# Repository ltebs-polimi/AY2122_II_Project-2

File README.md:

# ELECTRONIC TECHNOLOGIES AND BIOSENSORS LABORATORY, a.a. 2021/22

# Project 2 - Colombo L., D'Andrea M.

## Objective of the project

The objective of the project is to design and develop a system able to perform glucose monitoring using PSoC 5 as a potentiostat. Internal subdivision of the repository is as following:

- Case: contains the .stl files for the case design and printing
- Documents: contains all the bibliography related to the project and the datasheets of the hardware components
- Group2.cydsn: backup folder containing only the code related to glucose measurement, peripherals not included. **It is not to be intended as the folder of the whole project**
- PCB: contains schematic and board files for the PCB of the device
- Presentations: contains images of the project and final presentation
- Project_design: folder of the actual project
- PYTHON GUI: folder containing python scripts for the GUI
- Regression: folder containing the regression script used to find a calibration line and related images

**To open and run the project, open the Project_ETBL.cywrk file**

## Features implemented

Besides being capable of performing glucose measurements, the device hardware includes:

- RTC (DS3231): for real time tracking
- Bluetooth BR/EDR module (HC-05): for wireless communication
- External battery
- OLED screen (SSD1306 by Adafruit): to visualize data when GUI is not active
- External EEPROM (24LC512 by MicroChip): to store measurements

The assembled device and PCB are in the following images:
<br>

<br><br>

<br>

<br><br>

## PSoC code
The PSoC code is composed by:

- A global switch case handling the passage between the different OLED screens, up to the "Press the button to START the measurement" screen

- When the hardware button is pressed, the code automatically fetches potential values from the EEPROM and starts and amperometry scan. Basically "adcDacInterrupt" scans
a look-up table and sets the values to the DAC. At the same time the "adcAmpInterrupt" converts the values read by the ADC into current. In the end a glucose 
concentration value is retrieved by means of a proper calibration curve and the result is shown on the OLED screen.

- In case the GUI is started, the code allows to have a connection to the GUI and all the possible commands are managed. Among the different possibilities:
    - cyclic voltammetry (CV): another look up table is scanned by "dacInterrupt" and the "adcInterrupt" convertes the ADC readings into current. These values are sent to the GUI via bluetooth
    - chronoamperometry (CA): same as described before but in this case the current values are sent via bluetooth to the GUI
    - measurements history: measurements which were saved into the EEPROM (date, time and glucose value) at the end of a CA, are sent to the GUI via bluetooth

**see "GUI code" for further details**

## GUI code
The GUI is based on 3 different screens:

- first_screen.py: it allows to select between a user and a clinician

- user_screen.py:
    - Automatic COM port detection by sending a proper command to the PSoC and waiting for the expected answer
    - By pressing the "START MEASUREMENT" button, only a chronoamperometry will be started by sending a proper command to the psoc. The two ISRs needed for the chronoamperometry will be started. Finally the result of the measurement is displayed

- clinician_screen.py: 
    - Automatic COM port detection by sending a proper command to the PSoC and waiting for the expected answer
    - First tab (cyclic voltammetry): it is possible to setup all the required parameters for a cyclic voltammetry. Then it allows to visualize a real-time
    graph by pressing "DRAW"
    - Second tab (chronoamperometry): The clinician can decide to fetch a value of potential from the EEPROM or to start a CA based on the peak of potential identified 
    by the previous cyclic voltammetry. In both cases the real-time graph is shown
    - Third screen (Data visualization): it displays the result of the chronoamperometry scan, in terms of glucose concentration
    - Fourth tab (History): it allows to check the three latest measurements taken by the device. There is also the indication about the date and the time at which the 
    measurements have been taken

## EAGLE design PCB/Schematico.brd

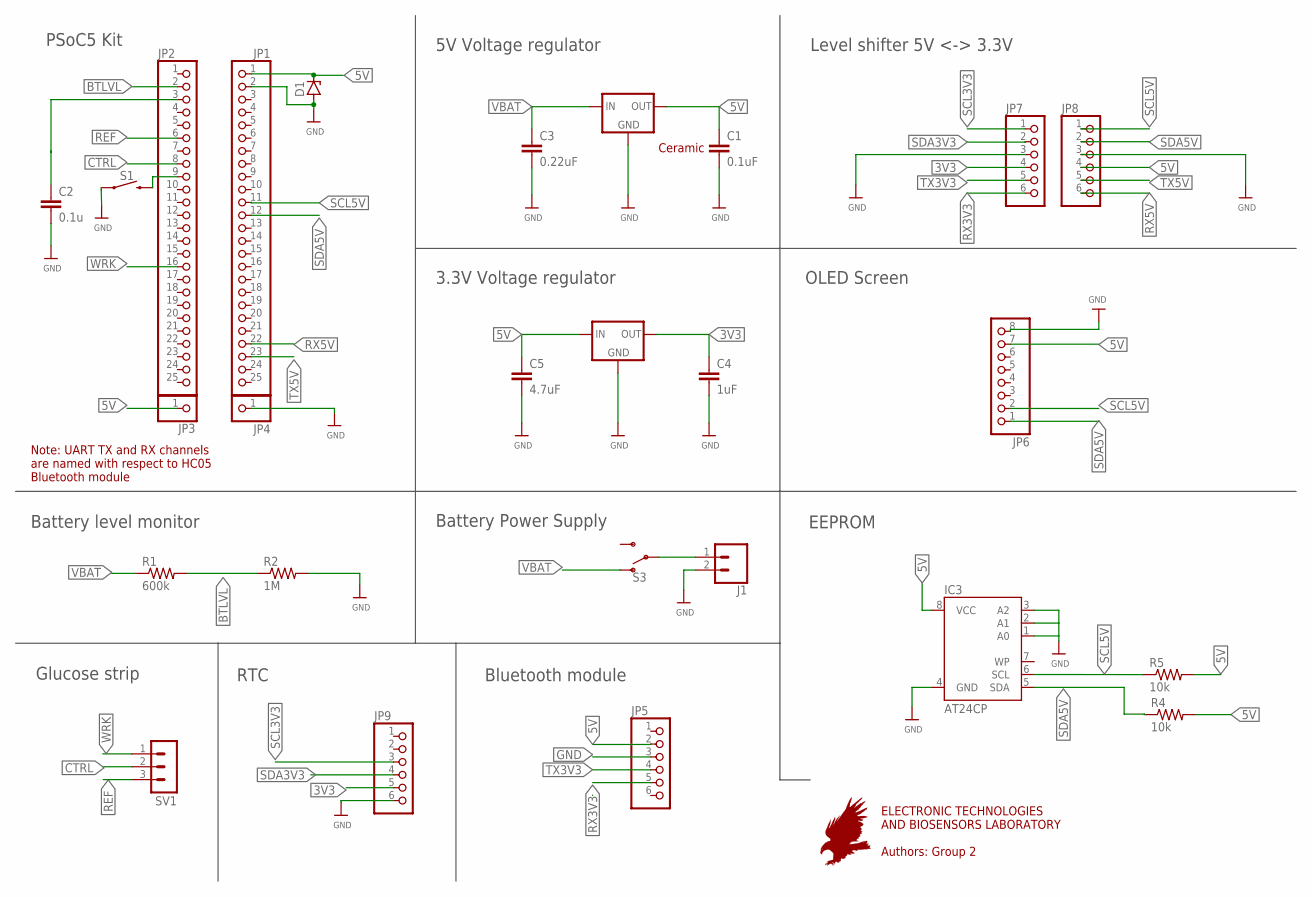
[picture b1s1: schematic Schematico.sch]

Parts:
C1: 0.1uF; C2.5-3
C2: 0.1u; C2.5-3
C3: 0.22uF; C2.5-3
C4: 1uF; C2.5-3
C5: 4.7uF; C2.5-3
D1: 1N821; DO35Z10
IC1, IC2: 78XXS
IC3: AT24CP; DIL08
J1: CONN_02; 1X02
JP1, JP2: PINHD-1X25; 1X25
JP3, JP4: PINHD-1X1; 1X01
JP5, JP7, JP8: PINHD-1X6B; 1X06-BIG
JP6: PINHD-1X8; 1X08
JP9: PINHD-1X6; 1X06
R1: 600k; 0204/7
R2: 1M; 0204/7
R4, R5: 10k; 0204/7
S1: MOMENTARY-SWITCH-SPST-PTH-6.0MM; TACTILE_SWITCH_PTH_6.0MM
S3: SWITCH-SPDT-PTH-11.6X4.0MM; SWITCH_SPDT_PTH_11.6X4.0MM
SV1: MA03-1

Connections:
3V3: C4.1, IC1.OUT, JP7.4, JP9.5
5V: C1.1, C5.1, D1.C, IC1.IN, IC2.OUT, IC3.8 (VCC), JP1.1, JP3.1, JP5.2, JP6.7, JP8.4, R4.2, R5.2
BTLVL: JP2.2, R1.2, R2.1
CTRL: JP2.8, SV1.2
GND: C1.2, C2.2, C3.2, C4.2, C5.2, D1.A, IC1.GND, IC2.GND, IC3.1 (A0), IC3.2 (A1), IC3.3 (A2), IC3.4 (GND), J1.2, JP1.2, JP4.1, JP5.3, JP6.8, JP7.3, JP8.3, JP9.6, R2.2, S1.1
unnamed: J1.1, S3.2
unnamed: C2.1, JP2.3
unnamed: JP2.9, S1.3 (2)
REF: JP2.6, SV1.3
RX3V3: JP5.5, JP7.6
RX5V: JP1.22, JP8.6
SCL3V3: JP7.1, JP9.3
SCL5V: IC3.6 (SCL), JP1.11, JP6.2, JP8.1, R5.1
SDA3V3: JP7.2, JP9.4
SDA5V: IC3.5 (SDA), JP1.12, JP6.1, JP8.2, R4.1
TX3V3: JP5.4, JP7.5
TX5V: JP1.23, JP8.5
VBAT: C3.1, IC2.IN, R1.1, S3.1 (O)
WRK: JP2.16, SV1.1

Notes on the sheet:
Level shifter 5V <-> 3.3V
OLED Screen
5V Voltage regulator
RTC
EEPROM
PSoC5 Kit
3.3V Voltage regulator
Battery Power Supply
Glucose strip
Bluetooth module
Note: UART TX and RX channels are named with respect to HC05 Bluetooth module
Battery level monitor
ELECTRONIC TECHNOLOGIES AND BIOSENSORS LABORATORY Authors: Group 2
Ceramic

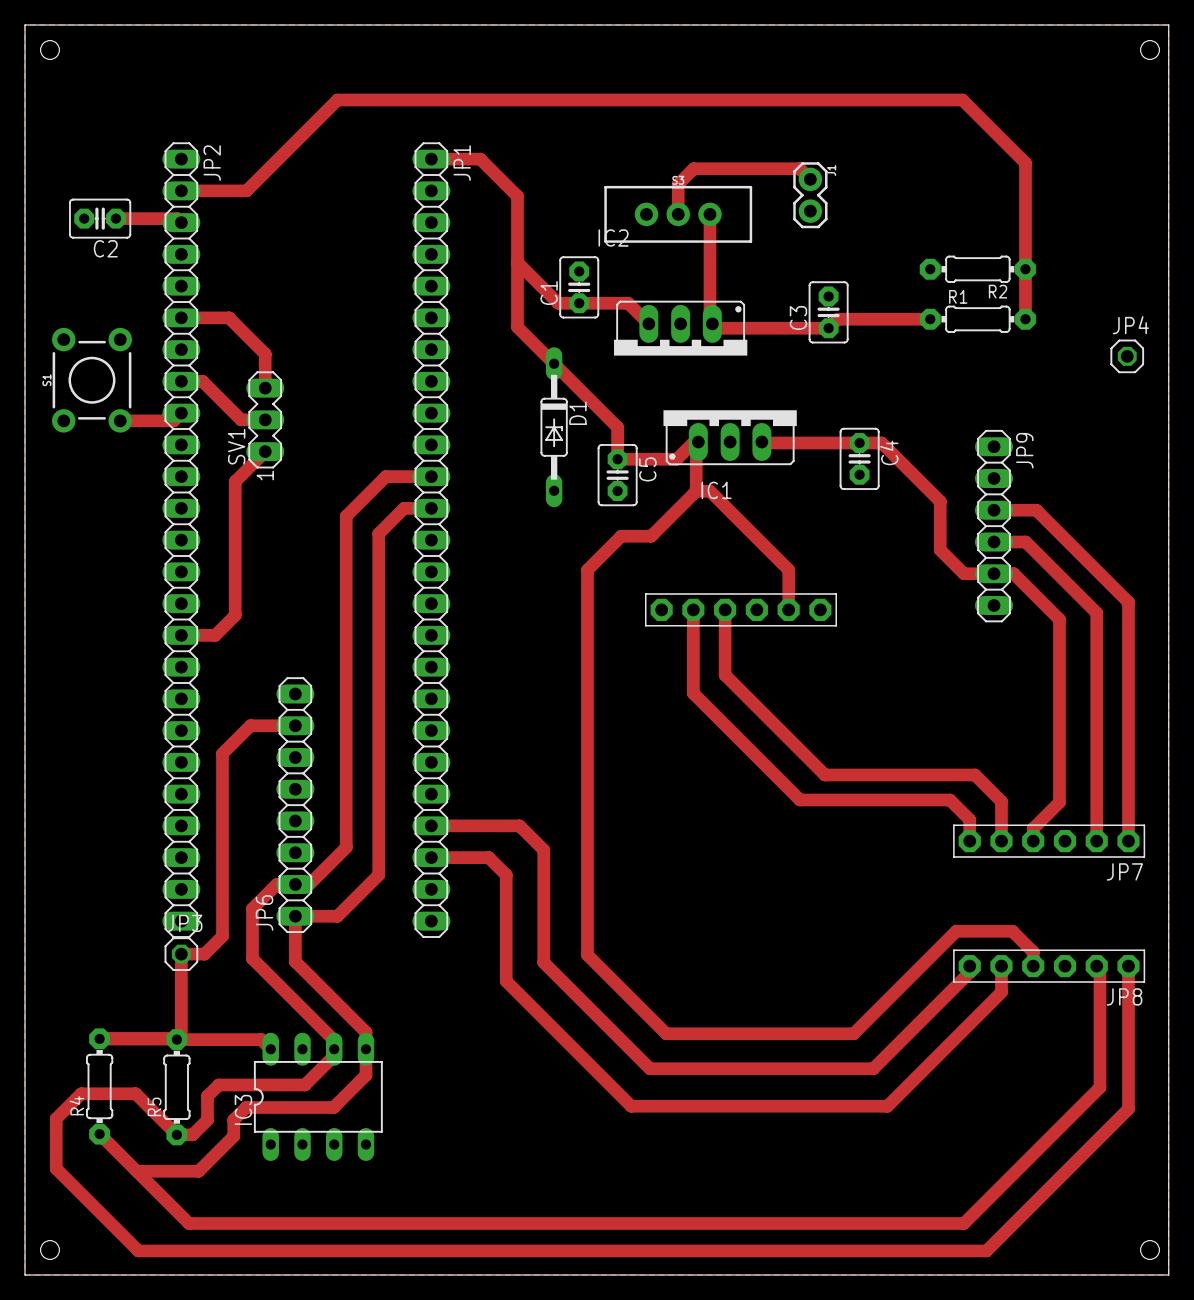
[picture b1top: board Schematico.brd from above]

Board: 2 copper layers, 91.5 x 100.0 mm, 26 parts (0 on the bottom side), 19 nets.

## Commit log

2022-05-09 Added base .gitignore
2022-05-17 First commit (in this repo)
2022-05-18 OLED Measurement interface finished
2022-05-18 Added comments and Loading screen initialization
2022-05-18 Working CV scan and GUI
2022-05-18 Working loading chronoamperometry OLED
2022-05-21 Working COM connection and real time graph
2022-05-23 Schematic update and globals for EEPROM
2022-05-25 Removed TIA calibration and updated real time graph
2022-05-25 Strip pins PCB
2022-05-25 First code merge except for main
2022-05-27 First code merge
2022-05-27 Added 10 samples MA filter
2022-06-04 EEPROM read and write functions and intermediate presentation
2022-06-05 Added automatic COM port detection in user screen
2022-06-08 Psoc switch case merged
2022-06-15 Addede Battery lvl monitor and timer
2022-06-15 Added chronoamperometry graph
2022-06-15 Gui with chronoamperometry
2022-06-15 Chronoamp on OLED
2022-06-16 Added project settings for float numbers
2022-06-18 Fetch values from EEPROM
2022-06-18 New presentation
2022-06-18 Fetch CV result test 1
2022-06-18 Working loading screen
2022-06-21 OLED Screen switched to GUI
2022-06-22 Chronoamp result @ 10s
2022-06-22 Look up table and CA initial potential
2022-06-22 Added calibration curve and result display
2022-06-22 Look up table
2022-06-28 Modified graphs axis references
2022-06-29 Case stl
2022-07-06 Assembled case, new calibr data
2022-07-07 New calibration and presentation
2022-07-07 Working measurement history
2022-07-07 Verbose comments added to the whole script, finished presentation
2022-07-07 Regression script added
2022-07-07 Added verbose comments to python GUIs
2022-07-07 Final presentation
2022-07-08 Added complete readme
2022-07-08 Final push

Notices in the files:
parts and their libraries:
SparkFun-Connectors: Licensing: Creative Commons ShareAlike 4.0 International - https://creativecommons.org/licenses/by-sa/4.0
microbuilder: This work is placed in the public domain, and may be freely used for commercial and non-commercial work with the following conditions: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
